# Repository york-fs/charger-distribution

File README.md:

# Charger Distribution Board

The charger distribution board lives in the charging box and interfaces with the TSAC distribution via a 23-pin AMPSEAL
connector.

[Latest Release](https://github.com/york-fs/charger-distribution/releases/latest)
[Interactive BOM](https://york-fs.github.io/charger-distribution/ibom.html)

## Cloning

A recursive clone must be used to download the `kicad-library` repository:

    git clone --recursive https://github.com/york-fs/charger-distribution.git

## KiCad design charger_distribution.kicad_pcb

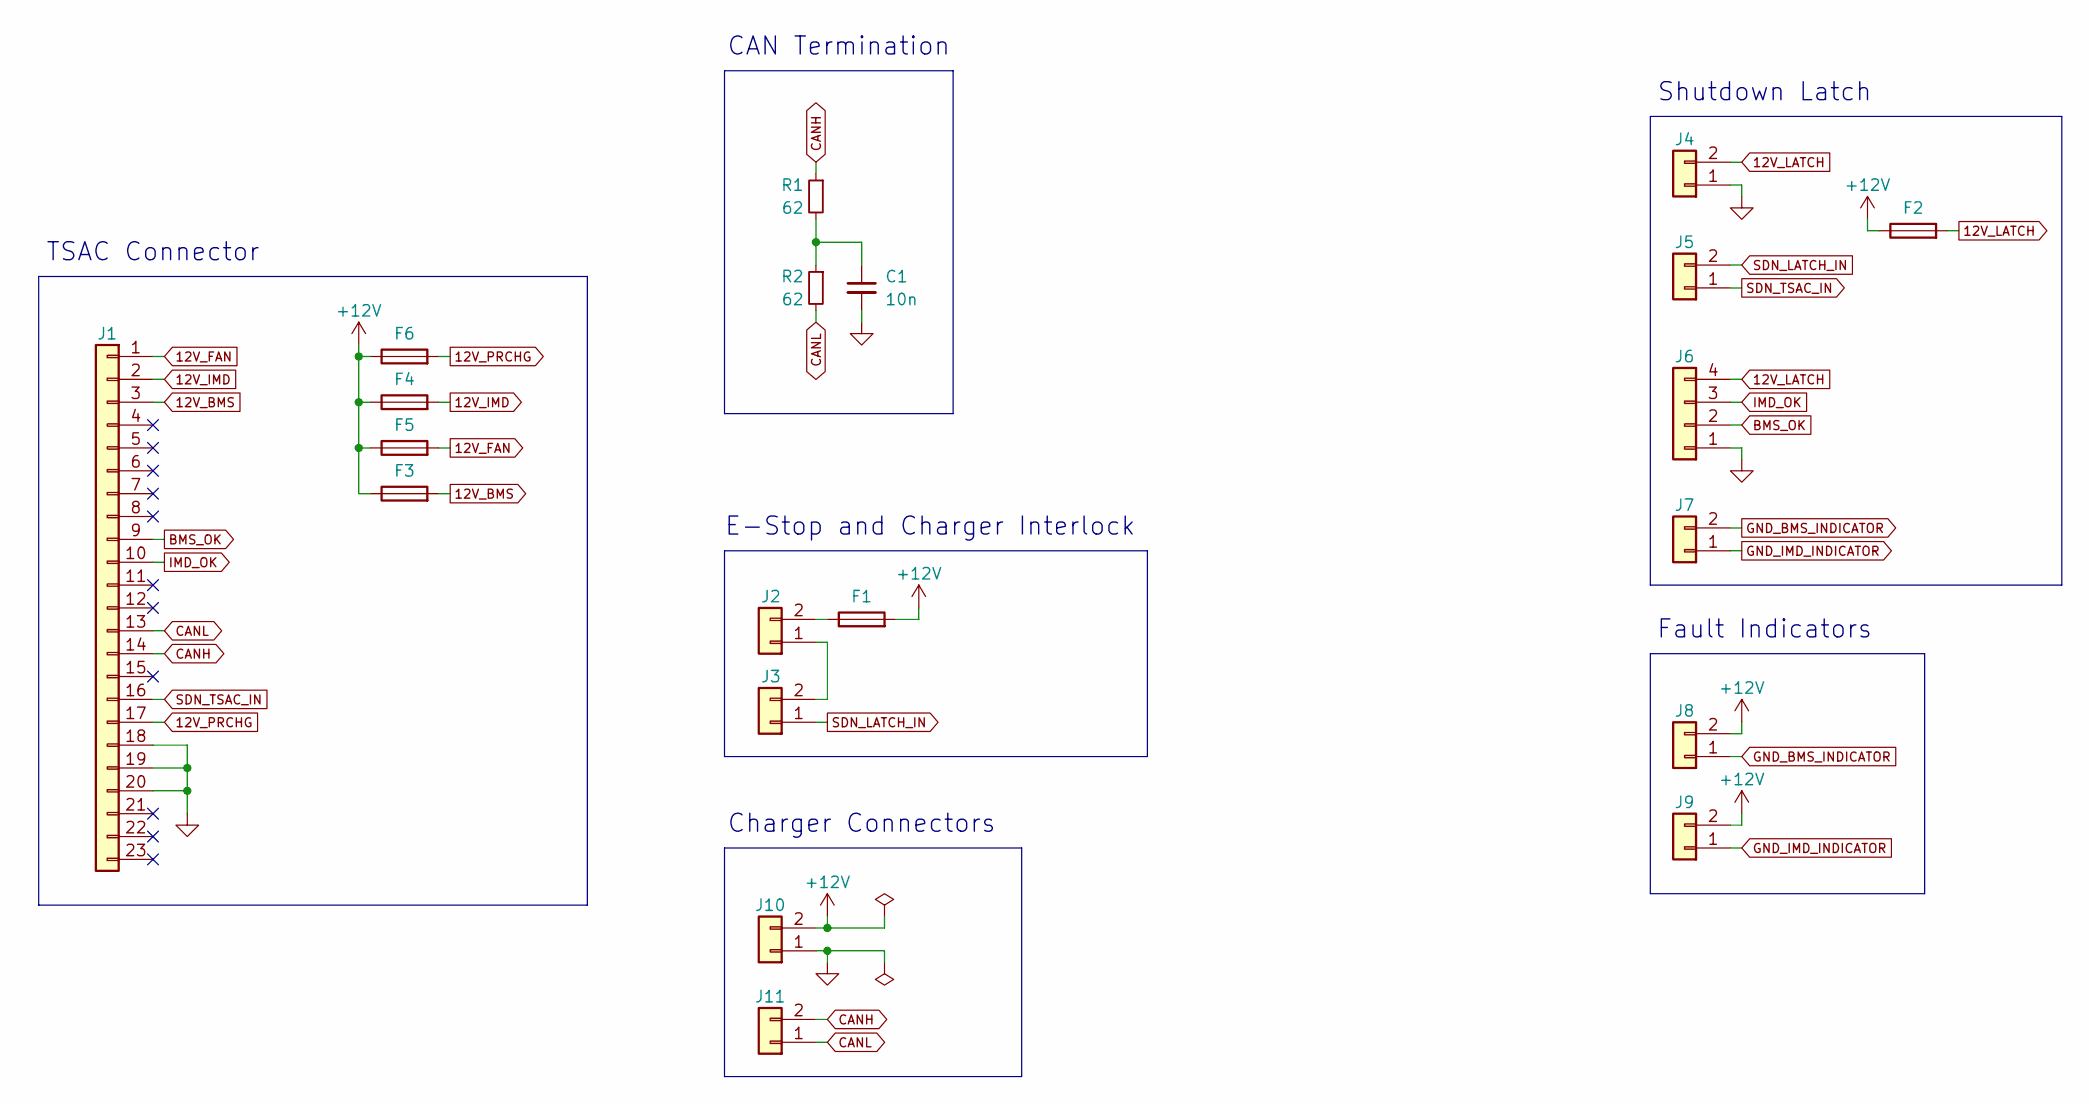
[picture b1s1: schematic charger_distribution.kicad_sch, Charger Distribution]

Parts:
C1: 10n; C_0603_1608Metric
F1, F2, F3, F4, F5, F6: Fuse; Keystone_3557-2; Mfr # 3557-2; DigiKey # 36-3557-2-ND
J1: Conn_01x23; AMPSEAL-23-776087; Mfr # 776087-1; DigiKey # A107007-ND
J2, J3, J5: Conn_01x02; MolexMicrofitPlus1x2; Mfr # 2157601032; DigiKey # 900-2157601032-ND
J4, J10: Conn_01x02; MolexMicrofitPlus1x2; Mfr # 2157601022; DigiKey # 900-2157601022-ND
J6: Conn_01x04; MolexMicrofitPlus1x4; Mfr # 2157601004; DigiKey # 900-2157601004-ND
J7, J8, J9, J11: Conn_01x02; MolexMicrofitPlus1x2; Mfr # 2157601002; DigiKey # 900-2157601002-ND
R1, R2: 62; R_1206_3216Metric; Mfr # CRCW120662R0JNEAHP; DigiKey # 541-62UACT-ND

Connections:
12V_BMS: F3.2, J1.3
12V_FAN: F5.2, J1.1
12V_IMD: F4.2, J1.2
12V_LATCH: F2.2, J4.2, J6.4
12V_PRCHG: F6.2, J1.17
+12V: F1.2, F2.1, F3.1, F4.1, F5.1, F6.1, J8.2, J9.2, J10.2
BMS_OK: J1.9, J6.2
CANH: J1.14, J11.2, R1.1
CANL: J1.13, J11.1, R2.2
GND: C1.2, J1.18, J1.19, J1.20, J4.1, J6.1, J10.1
GND_BMS_INDICATOR: J7.2, J8.1
GND_IMD_INDICATOR: J7.1, J9.1
IMD_OK: J1.10, J6.3
unnamed: C1.1, R1.2, R2.1
unnamed: J2.1, J3.2
unnamed: F1.1, J2.2
SDN_LATCH_IN: J3.1, J5.2
SDN_TSAC_IN: J1.16, J5.1

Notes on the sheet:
TSAC Connector
Shutdown Latch
E-Stop and Charger Interlock
Charger Connectors
Fault Indicators
CAN Termination

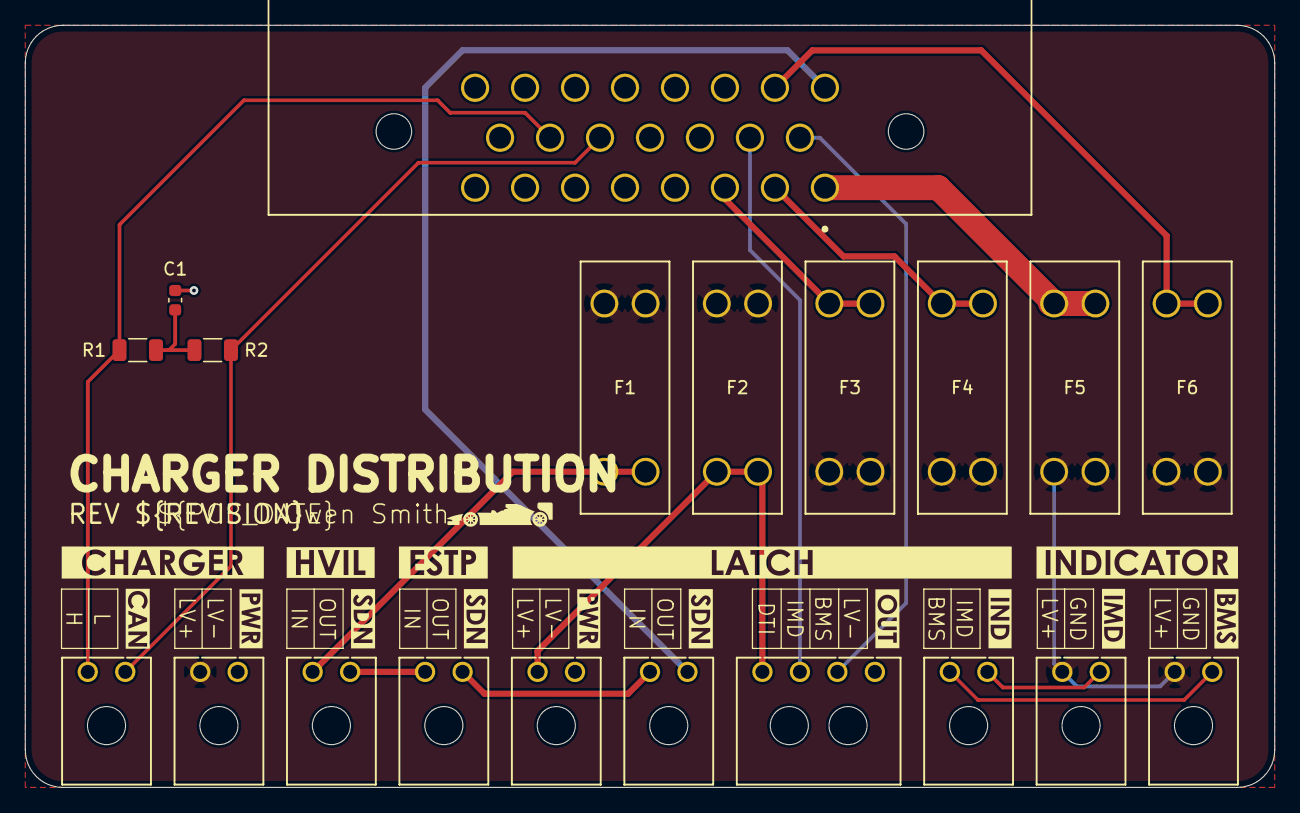
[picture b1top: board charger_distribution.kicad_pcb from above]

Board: 2 copper layers, 100.0 x 61.0 mm, 35 parts (0 on the bottom side), 18 nets.

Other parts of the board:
kibuzzard-6A47D7C5: G***; kibuzzard-6A47D7C5
kibuzzard-6A47D7FB: G***; kibuzzard-6A47D7FB
kibuzzard-6A47D9DC, kibuzzard-6A47D9DC#2, kibuzzard-6A47D9DC#3: G***; kibuzzard-6A47D9DC
kibuzzard-6A47D719: G***; kibuzzard-6A47D719
kibuzzard-6A47DA79: G***; kibuzzard-6A47DA79
kibuzzard-6A47DA91: G***; kibuzzard-6A47DA91
kibuzzard-6A47DAAC: G***; kibuzzard-6A47DAAC
kibuzzard-6A47DACD: G***; kibuzzard-6A47DACD
kibuzzard-6A47DADD: G***; kibuzzard-6A47DADD
kibuzzard-6A47DB8C: G***; kibuzzard-6A47DB8C
kibuzzard-6A47DB40: G***; kibuzzard-6A47DB40
kibuzzard-6A47DB72: G***; kibuzzard-6A47DB72
kibuzzard-6A47DBBA: G***; kibuzzard-6A47DBBA
